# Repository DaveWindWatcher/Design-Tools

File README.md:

# Design-Tools

Space for the Projects of the subject Dessigns Tool of the Elecronics Engineering Degree.

This course is mainly about PCB design and everything related to it. It is a very practical and application focused course, where students acquire skills in circuit and PCB design. From the conceptualization to the testing pahse and, eventually, the commercialization, going through block diagram and component gathering, schematic and layout and verification. 

### Contents
	I. Practiques
		
		Folder with Lab training, mostly about PCB design.
		
		I.I.	Practica1
		I.II.	Practica2
		I.III.	Practica3
		I.IV.	Practica4
		I.V.	Projecte

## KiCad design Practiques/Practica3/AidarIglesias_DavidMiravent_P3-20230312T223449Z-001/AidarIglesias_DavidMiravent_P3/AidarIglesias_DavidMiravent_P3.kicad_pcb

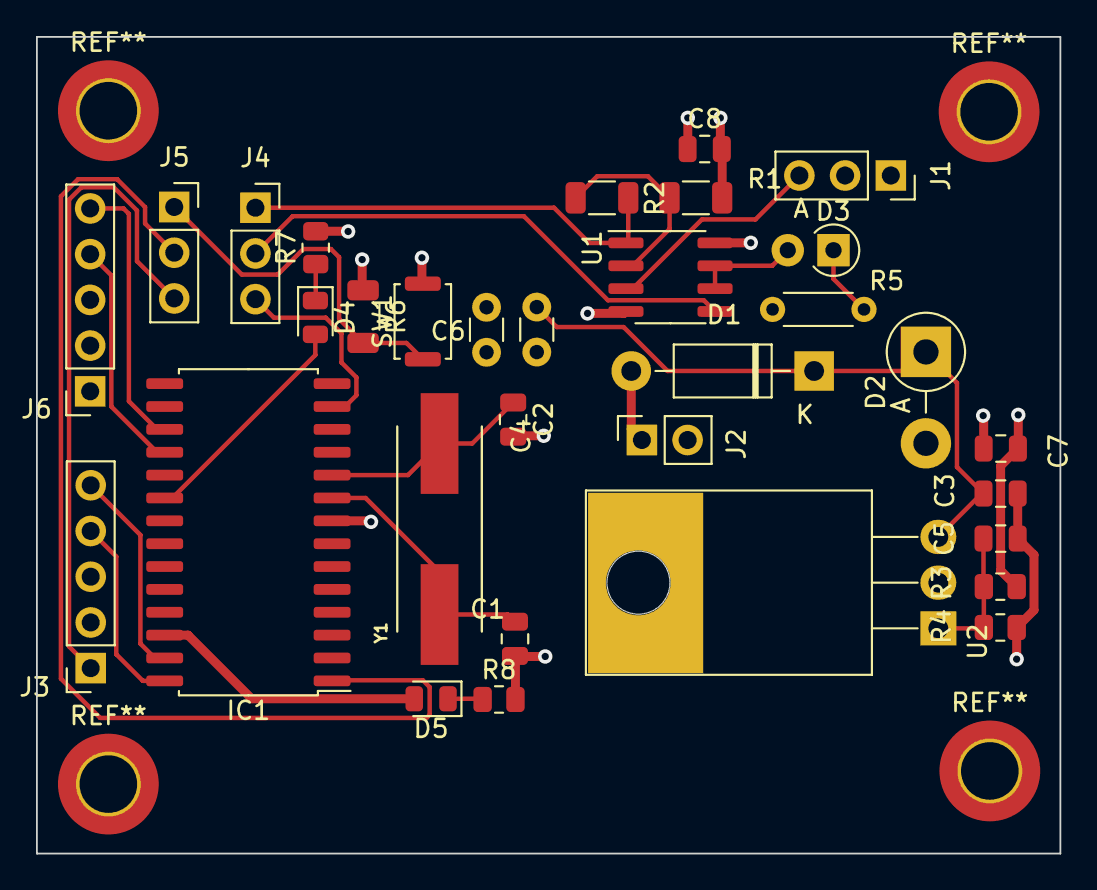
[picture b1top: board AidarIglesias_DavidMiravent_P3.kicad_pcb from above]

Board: 4 copper layers, 56.9 x 45.4 mm, 32 parts (0 on the bottom side), 25 nets.

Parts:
C1, C2: 30p; C_0805_2012Metric
C3, C5, C7, C8: 100n; C_0805_2012Metric
C4, C6: 1u; C_Disc_D3.0mm_W1.6mm_P2.50mm
D1: 1N4002; D_DO-41_SOD81_P10.16mm_Horizontal
D2: 15V; D_5W_P5.08mm_Vertical_AnodeUp
D3: LED; D_A-405_P2.54mm_Vertical_AnodeUp
D4: LED_RED; LED_0805_2012Metric
D5: LED_BLUE; LED_0805_2012Metric
IC1: PIC18F258-I_SO; SOIC-28W_7.5x17.9mm_P1.27mm
J1: ANALOG INPUT; PinSocket_1x03_P2.54mm_Vertical
J2: Screw_Terminal_01x02; PinSocket_1x02_P2.54mm_Vertical
J3: PROGRAMMING CON; PinSocket_1x05_P2.54mm_Vertical
J4: JP2; PinSocket_1x03_P2.54mm_Vertical
J5: JP1; PinSocket_1x03_P2.54mm_Vertical
J6: USART CON; PinSocket_1x05_P2.54mm_Vertical
R1: 100k; R_1206_3216Metric
R2: 68k; R_1206_3216Metric
R3: 2.2k; R_0805_2012Metric
R4: 1k; R_0805_2012Metric
R5: 1k; R_Axial_DIN0204_L3.6mm_D1.6mm_P5.08mm_Horizontal
R6: 4.7k; R_1206_3216Metric
R7: 220; R_0805_2012Metric
R8: 100; R_0805_2012Metric
SW1: SW_Push; SW_Push_SPST_NO_Alps_SKRK
U1: LT1492; SOIC-8_3.9x4.9mm_P1.27mm
U2: LM1117-ADJ; TO-220-3_Horizontal_TabDown
Y1: ABLS2-16.000MHZ-D4Y-T; XTAL_ABLS2-16.000MHZ-D4Y-T

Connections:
+VCC: C6.1, C7.1, C8.1, J1.1, J3.2, J6.3, R3.1, R6.1, R7.2, U1.8 (V+), U2.2 (VO), U2.4
/VAMP: J4.1, R2.2, U1.1
/V_{div}: C5.1, R3.2, R4.1, U2.1 (ADJ)
/V_{in}: C3.1, C4.1, D1.1 (K), D2.1 (K), U2.3 (VI)
/Vdd: D4.2 (A), IC1.20 (VDD)
/Vfbk: R1.2, R2.1, U1.2 (-)
/Vled: D3.1 (K), R5.1
/Vledb: D5.1 (K), R8.1
/Vledr: D4.1 (K), R7.1
/Vsw: J5.1, R6.2, SW1.1
GND: C1.2, C2.2, C3.2, C4.2, C5.2, C6.2, C7.2, C8.2, D2.2 (A), IC1.8 (VSS_1), J1.2, J2.2, J3.3, J6.1, R1.1, R4.2, R5.2, R8.2, SW1.2, U1.4 (V-)
MCLR: IC1.1 (~MCLR/VPP), J5.2
PGC: IC1.27 (RB6/PGC), J3.5
PGD: IC1.28 (RB7/PGD), J3.4
PGM: D5.2 (A), IC1.26 (RB5/PGM)
PROG_MCLR: J3.1, J5.3
PWM: IC1.13 (RC2/CCP1), J4.3
RX: IC1.18 (RC7/RX/DT), J6.4
TX: IC1.17 (RC6/TX/CK), J6.5
VBAT: D1.2 (A), J2.1
Vdrive: J4.2, U1.5 (+)
Vin: J1.3, U1.3 (+)
Vout: D3.2 (A), U1.6 (-), U1.7
XTAL1: C1.1, IC1.9 (OSC1/CLKI), Y1.1
XTAL2: C2.1, IC1.10 (OSC2/CLKO/RA6), Y1.2

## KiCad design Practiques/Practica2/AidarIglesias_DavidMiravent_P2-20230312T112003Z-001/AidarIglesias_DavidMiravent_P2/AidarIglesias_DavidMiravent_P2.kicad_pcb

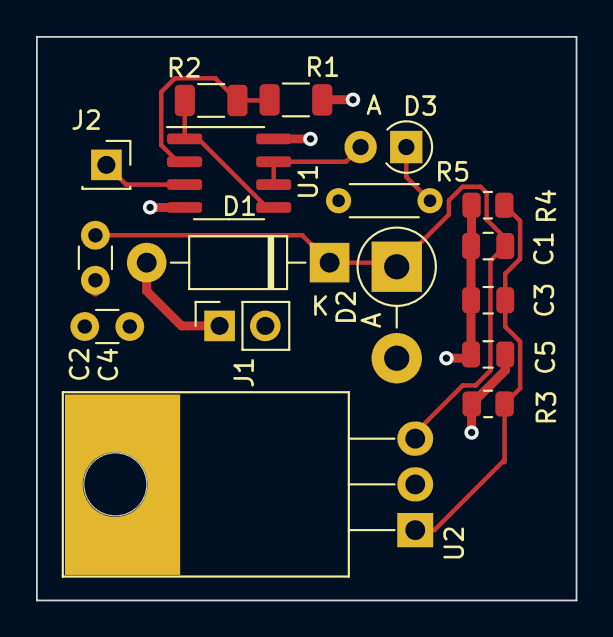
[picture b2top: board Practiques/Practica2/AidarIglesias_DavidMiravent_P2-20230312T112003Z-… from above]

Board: 4 copper layers, 30.0 x 31.3 mm, 17 parts (0 on the bottom side), 10 nets.

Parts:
C1, C3, C5: 100n; C_0805_2012Metric
C2, C4: 1u; C_Disc_D3.0mm_W1.6mm_P2.50mm
D1: 1N4002; D_DO-41_SOD81_P10.16mm_Horizontal
D2: 15V; D_5W_P5.08mm_Vertical_AnodeUp
D3: LED; D_A-405_P2.54mm_Vertical_AnodeUp
J1: Screw_Terminal_01x02; PinSocket_1x02_P2.54mm_Vertical
J2: Conn_01x01_Pin; PinSocket_1x01_P2.54mm_Vertical
R1: 100k; R_1206_3216Metric
R2: 68k; R_1206_3216Metric
R3: 2.2k; R_0805_2012Metric
R4: 1k; R_0805_2012Metric
R5: 1k; R_Axial_DIN0204_L3.6mm_D1.6mm_P5.08mm_Horizontal
U1: LT1492; SOIC-8_3.9x4.9mm_P1.27mm
U2: LM1117-ADJ; TO-220-3_Horizontal_TabDown

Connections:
+VCC: C4.1, C5.1, R3.1, U1.8 (V+), U2.2 (VO), U2.4
/V_{div}: C3.1, R3.2, R4.1, U2.1 (ADJ)
/V_{in}: C1.1, C2.1, D1.1 (K), D2.1 (K), U2.3 (VI)
GND: C1.2, C2.2, C3.2, C4.2, C5.2, D2.2 (A), J1.2, R1.1, R4.2, R5.2, U1.4 (V-)
unnamed: D3.1 (K), R5.1
unnamed: R1.2, R2.1, U1.2 (-)
VAMP: R2.2, U1.1, U1.5 (+)
VBAT: D1.2 (A), J1.1
Vin: J2.1, U1.3 (+)
Vout: D3.2 (A), U1.6 (-), U1.7

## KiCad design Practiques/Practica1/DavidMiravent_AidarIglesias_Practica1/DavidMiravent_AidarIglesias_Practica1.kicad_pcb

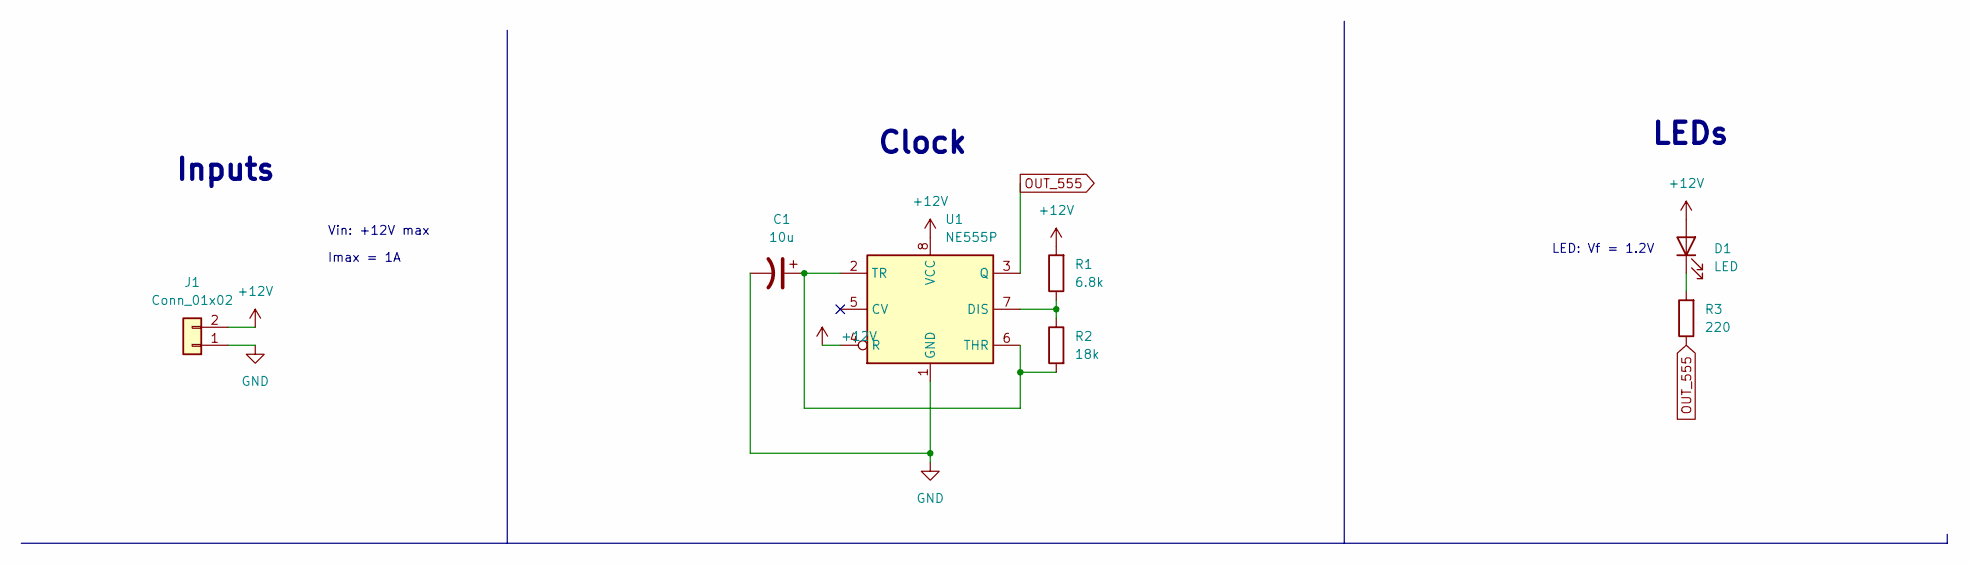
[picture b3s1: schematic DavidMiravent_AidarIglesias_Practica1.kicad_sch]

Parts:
C1: 10u; CP_Radial_D10.0mm_P3.80mm
D1: LED; LED_D5.0mm_FlatTop
J1: Conn_01x02; TerminalBlock_bornier-2_P5.08mm
R1: 6.8k; R_1206_3216Metric
R2: 18k; R_1206_3216Metric
R3: 220; R_1206_3216Metric
U1: NE555P; DIP-8_W7.62mm

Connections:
+12V: D1.2 (A), J1.2, R1.2, U1.4 (R), U1.8 (VCC)
GND: C1.2, J1.1, U1.1 (GND)
unnamed: C1.1, R2.2, U1.2 (TR), U1.6 (THR)
unnamed: D1.1 (K), R3.2
unnamed: R1.1, R2.1, U1.7 (DIS)
OUT_555: R3.1, U1.3 (Q)

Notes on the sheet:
Vin: +12V max
Inputs
Imax = 1A
LED: Vf = 1.2V
LEDs
Clock

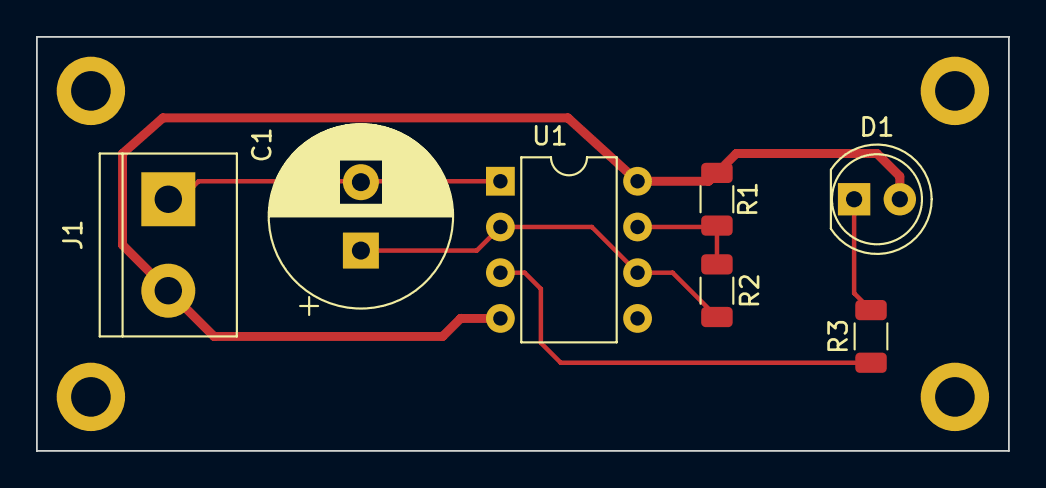
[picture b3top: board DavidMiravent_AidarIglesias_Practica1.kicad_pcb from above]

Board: 2 copper layers, 54.0 x 23.0 mm, 7 parts (0 on the bottom side), 6 nets.

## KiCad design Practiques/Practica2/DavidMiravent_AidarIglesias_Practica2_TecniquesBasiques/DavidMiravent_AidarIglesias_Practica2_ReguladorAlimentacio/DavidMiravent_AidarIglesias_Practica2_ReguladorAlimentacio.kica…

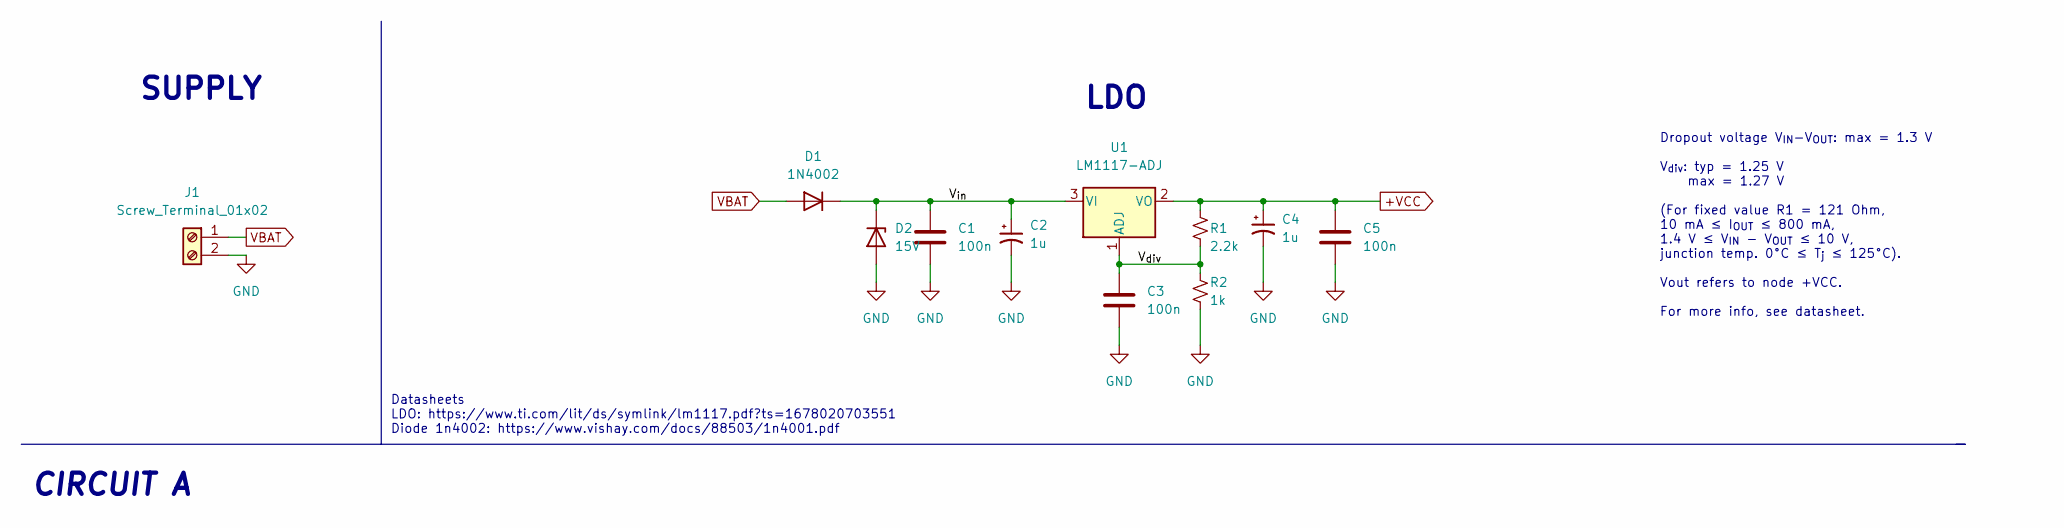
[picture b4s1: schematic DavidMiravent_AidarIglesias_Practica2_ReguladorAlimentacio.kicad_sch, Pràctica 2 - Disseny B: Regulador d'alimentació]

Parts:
C1, C3, C5: 100n; C_0805_2012Metric
C2, C4: 1u; C_Disc_D3.0mm_W1.6mm_P2.50mm
D1: 1N4002; D_DO-41_SOD81_P10.16mm_Horizontal
D2: 15V; D_5W_P5.08mm_Vertical_AnodeUp
J1: Screw_Terminal_01x02; Wago_734-132_1x02_P3.50mm_Vertical
R1: 2.2k; R_0805_2012Metric
R2: 1k; R_0805_2012Metric
U1: LM1117-ADJ; TO-220-3_Horizontal_TabDown

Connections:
+VCC: C4.1, C5.1, R1.1, U1.2 (VO)
/V_{div}: C3.1, R1.2, R2.1, U1.1 (ADJ)
/V_{in}: C1.1, C2.1, D1.1 (K), D2.1 (K), U1.3 (VI)
GND: C1.2, C2.2, C3.2, C4.2, C5.2, D2.2 (A), J1.2, R2.2
VBAT: D1.2 (A), J1.1

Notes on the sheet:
Dropout voltage V_{IN}-V_{OUT}: max = 1.3 V V_{div}: typ = 1.25 V max = 1.27 V (For fixed value R1 = 121 Ohm, 10 mA ≤ I_{OUT} ≤ 800 mA, 1.4 V ≤ V_{IN} - V_{OUT} ≤ 10 V, junction temp. 0°C ≤ T_{j} ≤ 125°C). Vout refers to node +VCC. For more info, see datasheet.
CIRCUIT A
SUPPLY
Datasheets LDO: https://www.ti.com/lit/ds/symlink/lm1117.pdf?ts=1678020703551 Diode 1n4002: https://www.vishay.com/docs/88503/1n4001.pdf
LDO

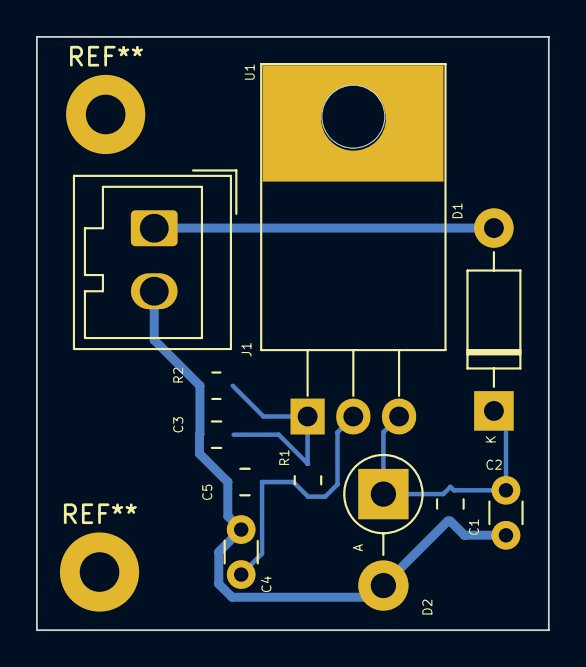
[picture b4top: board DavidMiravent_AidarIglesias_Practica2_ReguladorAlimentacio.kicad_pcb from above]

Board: 4 copper layers, 28.4 x 33.0 mm, 11 parts (0 on the bottom side), 5 nets.

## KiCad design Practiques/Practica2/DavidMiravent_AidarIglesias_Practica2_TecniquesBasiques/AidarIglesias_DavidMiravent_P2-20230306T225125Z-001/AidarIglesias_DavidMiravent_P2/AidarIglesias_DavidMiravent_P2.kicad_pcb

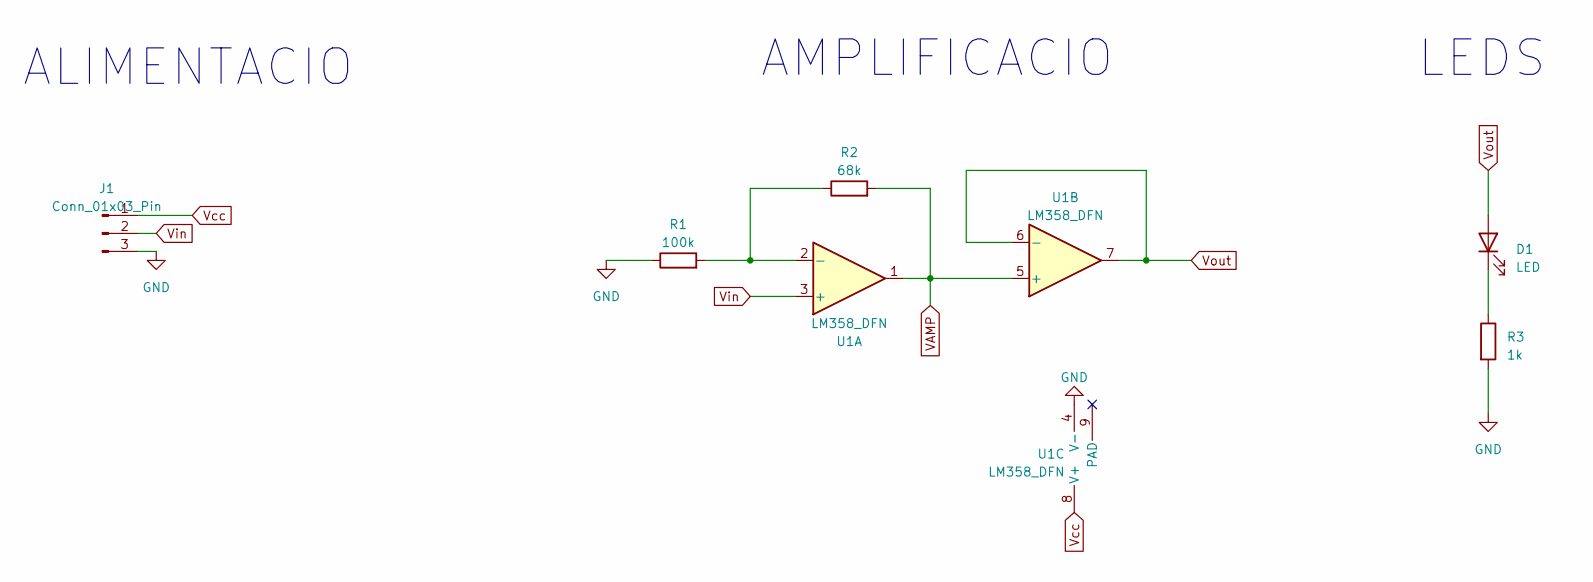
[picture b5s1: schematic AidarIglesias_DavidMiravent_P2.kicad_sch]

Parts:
D1: LED; D_A-405_P2.54mm_Vertical_AnodeUp
J1: Conn_01x03_Pin; PinHeader_1x03_P2.54mm_Vertical
R1: 100k; R_1206_3216Metric
R2: 68k; R_1206_3216Metric
R3: 1k; R_Axial_DIN0204_L3.6mm_D1.6mm_P5.08mm_Horizontal
U1: LM358_DFN; SOIC-8-1EP_3.9x4.9mm_P1.27mm_EP2.29x3mm

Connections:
GND: J1.3, R1.1, R3.2, U1.4 (V-)
unnamed: D1.1 (K), R3.1
unnamed: R1.2, R2.1, U1.2 (-)
VAMP: R2.2, U1.1, U1.5 (+)
Vcc: J1.1, U1.8 (V+)
Vin: J1.2, U1.3 (+)
Vout: D1.2 (A), U1.6 (-), U1.7

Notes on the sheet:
AMPLIFICACIO
LEDS
ALIMENTACIO

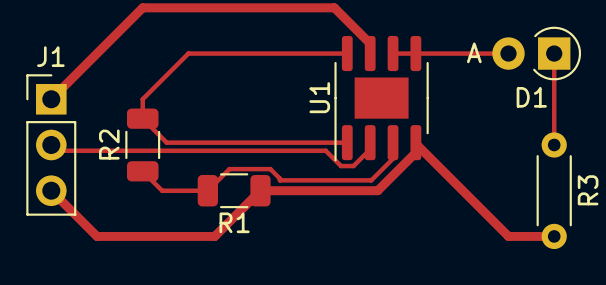
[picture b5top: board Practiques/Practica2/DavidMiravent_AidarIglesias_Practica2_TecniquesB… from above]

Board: 2 copper layers, 6 parts (0 on the bottom side), 7 nets.

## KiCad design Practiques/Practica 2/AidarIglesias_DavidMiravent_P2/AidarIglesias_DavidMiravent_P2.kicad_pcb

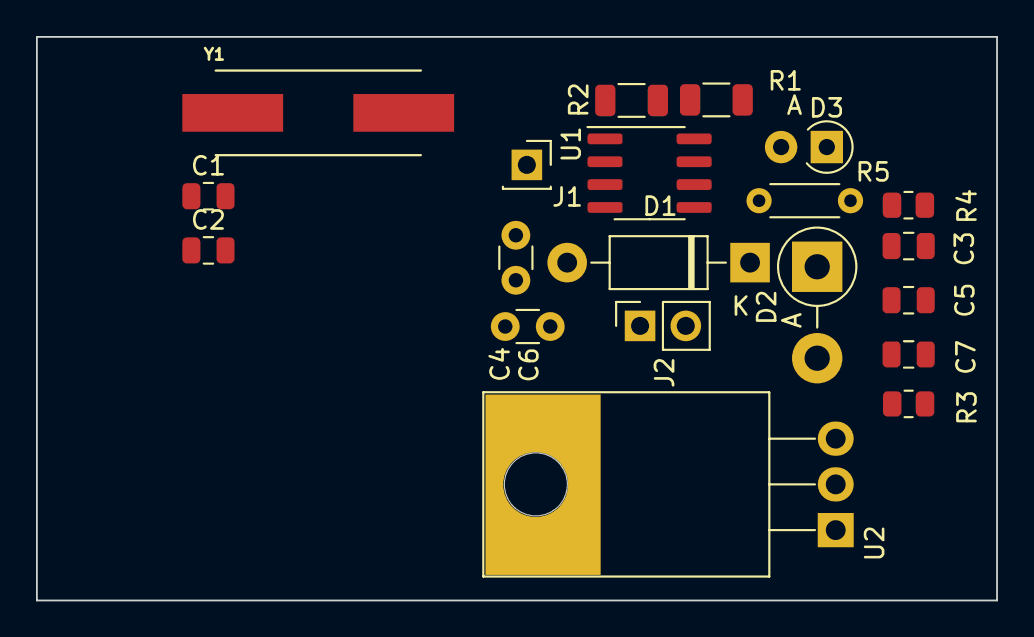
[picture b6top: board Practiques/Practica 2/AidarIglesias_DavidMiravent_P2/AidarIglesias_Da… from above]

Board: 4 copper layers, 53.3 x 31.3 mm, 20 parts (0 on the bottom side), 12 nets, no tracks yet.

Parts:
C1, C2: 30p; C_0805_2012Metric
C3, C5, C7: 100n; C_0805_2012Metric
C4, C6: 1u; C_Disc_D3.0mm_W1.6mm_P2.50mm
D1: 1N4002; D_DO-41_SOD81_P10.16mm_Horizontal
D2: 15V; D_5W_P5.08mm_Vertical_AnodeUp
D3: LED; D_A-405_P2.54mm_Vertical_AnodeUp
J1: Conn_01x01_Pin; PinSocket_1x01_P2.54mm_Vertical
J2: Screw_Terminal_01x02; PinSocket_1x02_P2.54mm_Vertical
R1: 100k; R_1206_3216Metric
R2: 68k; R_1206_3216Metric
R3: 2.2k; R_0805_2012Metric
R4: 1k; R_0805_2012Metric
R5: 1k; R_Axial_DIN0204_L3.6mm_D1.6mm_P5.08mm_Horizontal
U1: LT1492; SOIC-8_3.9x4.9mm_P1.27mm
U2: LM1117-ADJ; TO-220-3_Horizontal_TabDown
Y1: ABLS2-16.000MHZ-D4Y-T; XTAL_ABLS2-16.000MHZ-D4Y-T

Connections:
+VCC: C6.1, C7.1, R3.1, U1.8 (V+), U2.2 (VO), U2.4
/V_{div}: C5.1, R3.2, R4.1, U2.1 (ADJ)
/V_{in}: C3.1, C4.1, D1.1 (K), D2.1 (K), U2.3 (VI)
GND: C1.2, C2.2, C3.2, C4.2, C5.2, C6.2, C7.2, D2.2 (A), J2.2, R1.1, R4.2, R5.2, U1.4 (V-)
unnamed: D3.1 (K), R5.1
unnamed: R1.2, R2.1, U1.3 (+)
VAMP: R2.2, U1.1, U1.6 (-)
VBAT: D1.2 (A), J2.1
Vin: J1.1, U1.2 (-)
Vout: D3.2 (A), U1.5 (+), U1.7
XTAL1: C1.1, Y1.1
XTAL2: C2.1, Y1.2

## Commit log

2023-02-23 Practica 1
2023-02-23 'Carpeta_General'
2023-03-13 Posada_a_Punt
2023-03-13 Mod_P3_13_03_23
2023-03-13 Mod_P3_13_03_23_22_26
2023-03-13 Mod_13_03_23_22_56
2023-03-13 Mod_14_03_23_00_44
2023-03-15 Mod_15_03_23_13_08
2023-03-17 Mod_README_17_03_23_10_09
2023-03-17 prova
2023-03-17 esborrem
2023-03-17 ashdkjah
2023-03-17 asumbele
2023-03-17 fotososciloscopip4
2023-03-19 Mod_19_03_23_17_19
2023-03-22 Mod_22_03_23_19_20
